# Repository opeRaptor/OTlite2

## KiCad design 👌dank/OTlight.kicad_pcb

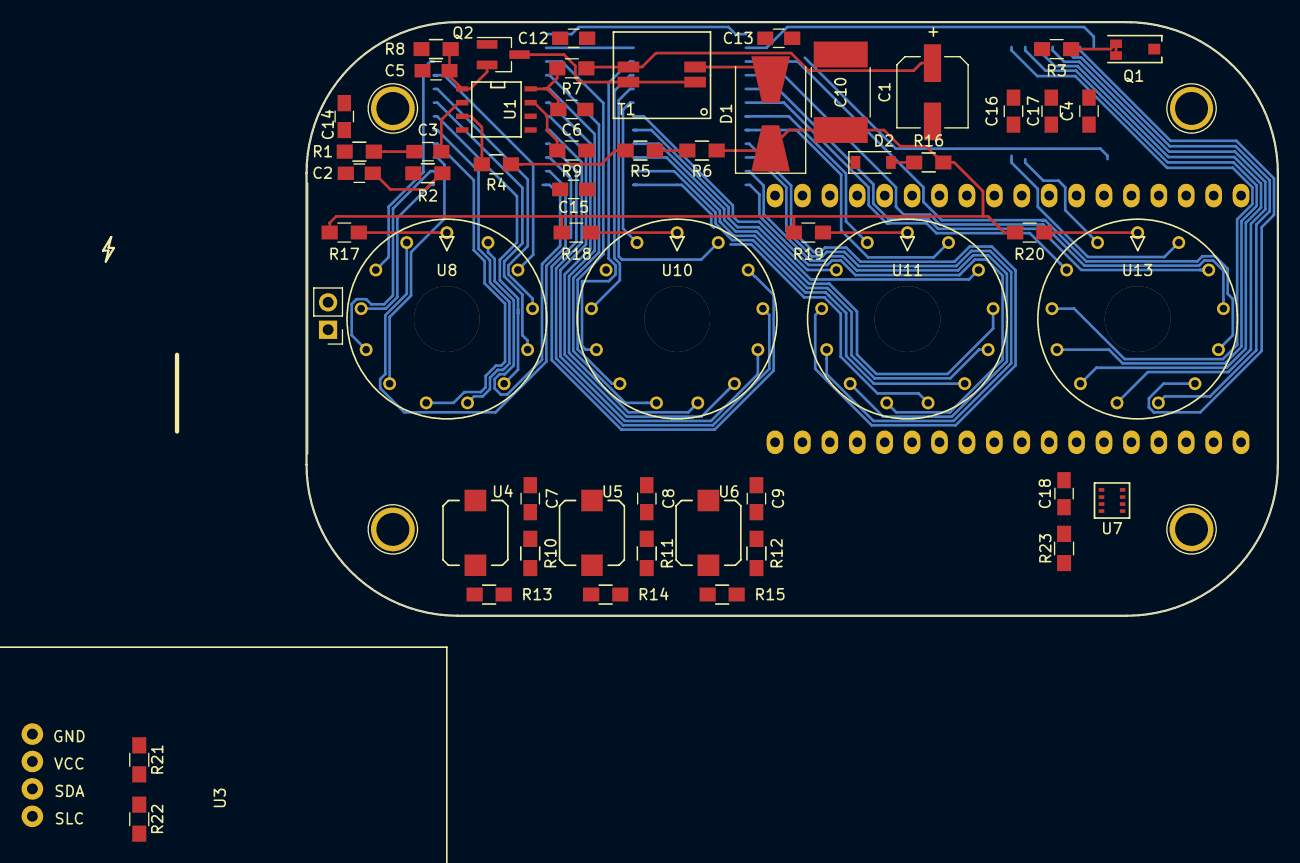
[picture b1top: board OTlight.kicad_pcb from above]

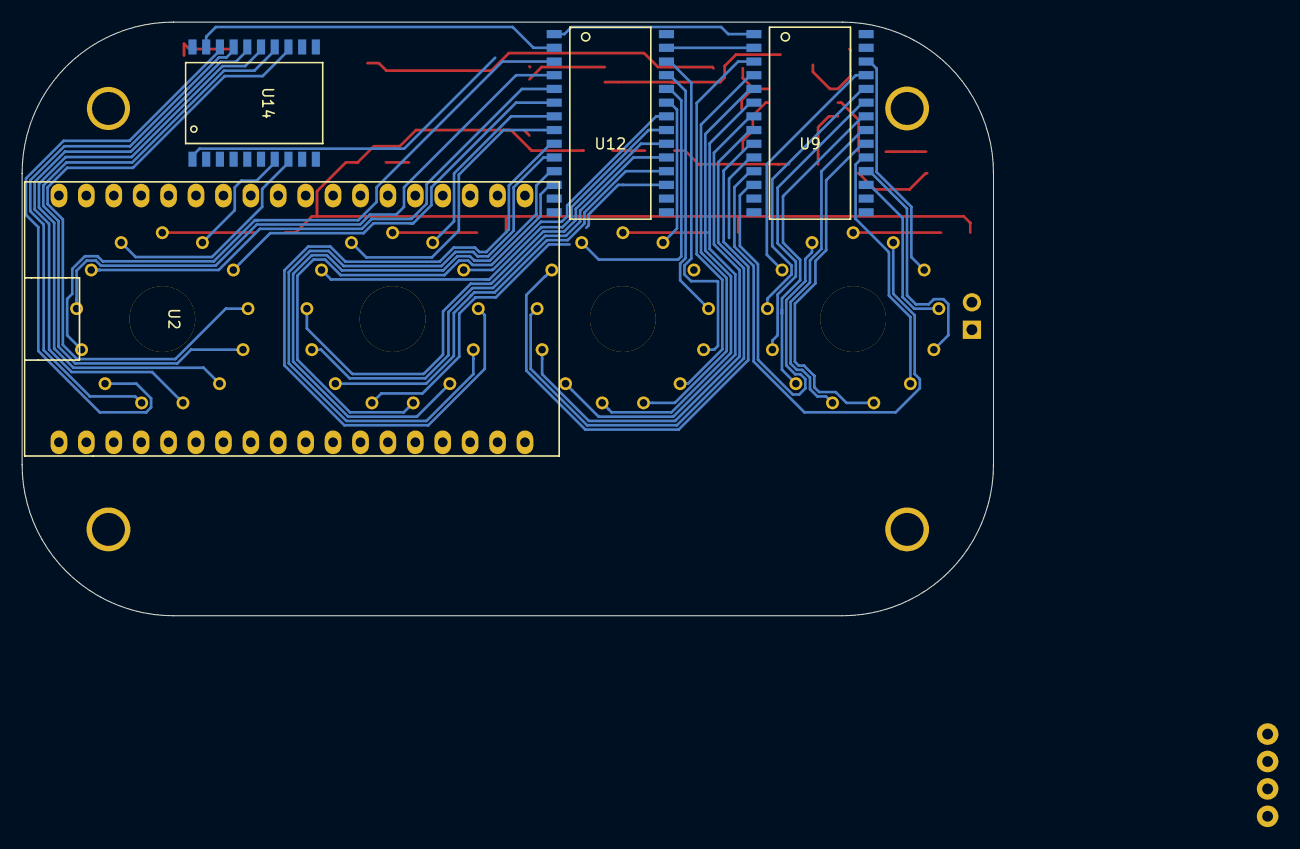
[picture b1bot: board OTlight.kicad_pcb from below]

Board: 2 copper layers, 90.0 x 55.0 mm, 60 parts (4 on the bottom side), 83 nets.

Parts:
C1: 220u; CP_Elec_6.3x7.7
C2: 0.001; C_0805_HandSoldering
C3, C6, C7, C8, C9, C18: 0.1u; C_0805_HandSoldering
C4: 10u; C_0805_HandSoldering
C5: 0.01u; C_0805_HandSoldering
C10: 1u; C_2220_HandSoldering
C12, C13, C14, C15, C16, C17: C_Small; C_0805_HandSoldering
D1: STPS4S200; D_SMB-SMC_Universal_Handsoldering
D2: D_Zener_Small_ALT; D_SOD-123
P1: CONN_01X02; Pin_Header_Straight_1x02_Pitch2.54mm
Q1: TEMT6000
Q2: RSR030N06TL; SOT-23_Handsoldering
R1: 1K; R_0805_HandSoldering
R2: 13K; R_0805_HandSoldering
R3, R10, R11, R12, R13, R14, R15, R16, R17, R18, R19, R20, R21, R22, R23: R_Small; R_0805_HandSoldering
R4: 1M; R_0805_HandSoldering
R5: 820K; R_0805_HandSoldering
R6: 24K; R_0805_HandSoldering
R7: 20; R_0805_HandSoldering
R8: 0.1; R_0805_HandSoldering
R9: 15K; R_0805_HandSoldering
T1: TRANSFO; CTX02-18714-R
U1: LM3478; SOIC-8-N
U2: ESP32; ESP32-OLED
U3: DS3231
U4, U5, U6: PushButton; SPEH120100
U7: bareBME280; BME280bare
U8, U10, U11, U13: IN-14; bearing-7mm
U9, U12: MAX6931; SW-28
U14: MAX6920; SW-20

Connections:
+3V3: C18.2, Q1.1, R21.1, R22.1, R23.2, U2.3, U3.2, U4.2, U5.2, U6.2, U7.2, U7.6, U7.8, U9.28, U12.28, U14.20
+5V: C1.1, C4.1, R7.1, T1.3, U2.2
/CLK: U9.15, U12.15, U14.11
/DIN: U2.19, U9.27
/HVout: C10.1, D1.1, P1.1, R6.1, R16.1, R17.1, R18.1, R19.1, R20.1
/LOAD: U9.16, U12.16, U14.12
GND: C1.2, C2.2, C4.2, C5.2, C6.2, C7.2, C8.2, C9.2, C10.2, C12.1, C13.1, C14.2, C15.2, C16.2, C17.1, C18.1, D2.1, P1.2, R1.2, R2.2, R3.2, R8.2, R9.1, R13.2, R14.2, R15.2, U1.4, U1.5, U2.1, U3.1, U7.1, U7.7, U9.13, U9.14, U12.13, U12.14, U14.9, U14.10
unnamed: C2.1, R2.1, R4.2, U1.3
unnamed: C3.1, U1.2
unnamed: C3.2, R1.1
unnamed: C5.1, Q2.2, R8.1, U1.1
unnamed: C6.1, R7.2, U1.8
unnamed: C7.1, R10.1
unnamed: C8.1, R11.1
unnamed: C9.1, R12.1
unnamed: D1.2, T1.2
unnamed: Q1.2, R3.1
unnamed: Q2.1, U1.6
unnamed: Q2.3, T1.1, T1.4
unnamed: R4.1, R5.2
unnamed: R5.1, R6.2
unnamed: R9.2, U1.7
unnamed: R10.2, R13.1, U4.1
unnamed: R11.2, R14.1, U5.1
unnamed: R12.2, R15.1, U6.1
unnamed: R16.2, U9.1, U12.1, U14.1
unnamed: R17.2, U8.1
unnamed: R18.2, U10.1
unnamed: R19.2, U11.1
unnamed: R20.2, U13.1
unnamed: R21.2, U3.3, U7.3
unnamed: R22.2, U3.4, U7.4
unnamed: R23.1, U7.5
unnamed: U8.2, U9.12
unnamed: U8.3, U9.25
unnamed: U8.4, U9.24
unnamed: U8.5, U9.23
unnamed: U8.6, U9.22
unnamed: U8.7, U9.21
unnamed: U8.8, U9.20
unnamed: U8.9, U9.19
unnamed: U8.10, U9.18
unnamed: U8.11, U9.17
unnamed: U8.12, U9.26
unnamed: U8.13, U9.11
unnamed: U10.2, U12.24
unnamed: U9.9, U10.3
unnamed: U9.8, U10.4
unnamed: U9.7, U10.5
unnamed: U9.6, U10.6
unnamed: U9.5, U10.7
unnamed: U9.4, U10.8
unnamed: U9.3, U10.9
unnamed: U10.10, U12.26
unnamed: U10.11, U12.25
unnamed: U9.10, U10.12
unnamed: U10.13, U12.23
unnamed: U11.2, U12.8
unnamed: U11.3, U12.21
unnamed: U11.4, U12.20
unnamed: U11.5, U12.19
unnamed: U11.6, U12.18
unnamed: U11.7, U12.17
unnamed: U11.8, U12.12
unnamed: U11.9, U12.11
unnamed: U11.10, U12.10
unnamed: U11.11, U12.9
unnamed: U11.12, U12.22
unnamed: U11.13, U12.7
unnamed: U12.2, U14.19
unnamed: U12.3, U13.5
unnamed: U12.4, U13.4
unnamed: U12.5, U13.3
unnamed: U12.6, U13.12
unnamed: U9.2, U12.27
unnamed: U13.2, U14.8
unnamed: U13.6, U14.18
unnamed: U13.7, U14.17
unnamed: U13.8, U14.16
unnamed: U13.9, U14.15
unnamed: U13.10, U14.14
unnamed: U13.11, U14.13
unnamed: U13.13, U14.7

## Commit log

2018-04-27 Initial push from O;Tl
2018-04-27 Added drivers and shift registers
2018-07-22 Dot drivers added.
